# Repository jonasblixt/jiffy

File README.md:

# jiffy
IMX6UL Development board

This is a work in progress. The first version of the hardware works fine but some simplifications and polishing will be done for the R2 release.

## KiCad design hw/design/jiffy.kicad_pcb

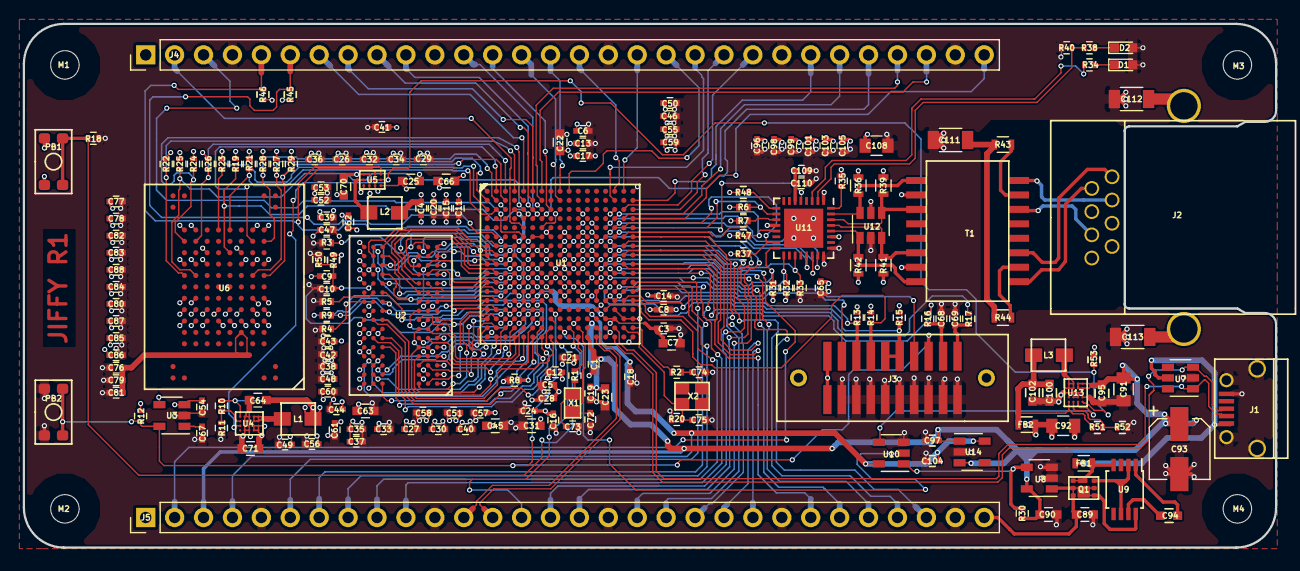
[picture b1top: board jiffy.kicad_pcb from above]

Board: 4 copper layers, 110.0 x 46.0 mm, 199 parts (0 on the bottom side), 190 nets.

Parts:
C1, C3, C4, C5, C6, C9, C10, C11, C12, C13, C14, C15, C16, C17, C18, C19, C20, C21, C24, C26, C27, C28, C29, C30, C32, C33, C34, C35, C36, C37, C38, C39, C40, C41, C42, C43, C44, C46, C47, C48, C49, C50, C51, C52, C53, C54, C55, C56, C57, C58, C59, C60, C61, C62, C65, C76, C77, C78, C79, C80, C81, C82, C83, C84, C85, C86, C87, C88, C96, C97, C98, C99, C101, C103, C104, C105, C109, C110: C0402_1u_10Vdc_X5R; C_0402
C7, C22, C23, C25, C31, C45: C0603_22u_10Vdc_X5R; C_0603
C8: C0402_10u_2.5Vdc_X5R; C_0402
C63, C64, C66, C71, C95, C100, C102: C0603_10u_10Vdc_X7R; C_0603
C67: C0402_100n_100Vdc_X5R; C_0402
C68, C69: C0402_10n_50Vdc_X7R; C_0402
C70: C0603_4u7_16Vdc_X7R; C_0603
C72, C73, C74, C75: C0402_15p_100Vdc_C0G; C_0402
C89, C90, C94: C0603_1u_25Vdc_X7R; C_0603
C91, C92: C0805_10u_25Vdc_X7R; C_0805
C93: PCAP_220u_11; CP_Elec_5x5.3
C108: C0805_20n_50Vdc_X7R; C_0805
C111, C112, C113: C1206_1n5_1000Vdc_X7R; C_1206
D1, D2: LED0402_SML-P11MTT86; LED_0603
FB1, FB2: BL0603_BLM18KG121TN1D; R_0603
J1: DX4R005JJ2R1800; USB_Micro-B
J2: RJE72-188-1401
J3: TFM-110-02-S-D-WT
J4, J5: Conn_01x30; Pin_Header_Straight_1x30_Pitch2.54mm
L1, L3: IHLP1212_470n_0; IHLP1212
L2: IHLP1212_1u_1; IHLP1212
M1, M2, M3, M4: MHNP_2.5mm; MH_2.5mm
PB1, PB2: KMR631NGULCLFS; kmr6
Q1: CSD17313Q2Q1; SON6_EP
R1, R2, R9, R16, R17: R0402_100R; R_0402
R3, R4, R10, R18, R19, R21, R22, R24, R25, R26, R27, R28, R29, R51, R53: R0402_46k40; R_0402
R5, R8: R0402_240R; R_0402
R6, R7, R12, R30, R33, R37, R40, R45, R46, R47, R48: R0402_10k; R_0402
R11: R0402_66k50; R_0402
R13, R14, R15: R0402_100k; R_0402
R20: R0402_2M20; R_0402
R23: R0402_22R; R_0402
R31, R32, R49, R50: R0402_1k50; R_0402
R34, R38: R0402_330R; R_0402
R35: R0402_12k10; R_0402
R36, R39, R41, R42: R0603_49R90; R_0603
R43, R44: R0603_75R; R_0603
R52: R0402_14k70; R_0402
T1: PT61018PEL; Ethernet_trafo_so16w
U1: MCIMX6G2AVM07; LFBGA289
U2: MT41K512M16HA-125; BGA-96_pitch0.8mm_dia0.4mm
U3: LP3470M5-3.08; SOT-23-5
U4, U13: FAN53541; WLCSP20
U5: FAN5355UC00; WLCSP12
U6: FEMC004GTTE7-T13-17; 100LBGA_DQ
U7, U12: USBLC6-4; SOT-23-6
U8: NCP360SNAET1G; SOT-23-5
U9: LM74610; TSSOP-8_3x3mm_Pitch0.65mm
U10: SN74AHC1G08; SOT-23-5
U11: LAN8710; QFN-32-1EP_5x5mm_Pitch0.5mm
U14: NCV551SN33T1G; SOT-23-5
X1: NX2012SA-32.768K-STD-MUB-1; NX2012
X2: NX2520SA-24.000000MHZ; NX2520

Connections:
/CPU/A0: U1.L5, U2.N3
/CPU/A1: U1.H2, U2.P7
/CPU/A2: U1.K1, U2.P3
/CPU/A3: U1.M2, U2.N2
/CPU/A4: U1.K4, U2.P8
/CPU/A5: U1.L1, U2.P2
/CPU/A6: U1.G2, U2.R8
/CPU/A7: U1.H4, U2.R2
/CPU/A8: U1.J4, U2.T8
/CPU/A9: U1.L2, U2.R3
/CPU/A10: U1.M4, U2.L7
/CPU/A11: U1.K3, U2.R7
/CPU/A12: U1.L4, U2.N7
/CPU/A13: U1.H3, U2.T3
/CPU/A14: U1.G1, U2.T7
/CPU/A15: U1.K5, U2.M7
/CPU/BM0: PB1.2, R18.1, U1.T10
/CPU/DQ0: U1.T4, U2.E3
/CPU/DQ1: U1.U6, U2.F7
/CPU/DQ2: U1.T6, U2.F2
/CPU/DQ3: U1.U7, U2.F8
/CPU/DQ4: U1.U8, U2.H7
/CPU/DQ5: U1.T8, U2.H8
/CPU/DQ6: U1.T5, U2.G2
/CPU/DQ7: U1.U4, U2.H3
/CPU/DQ8: U1.U2, U2.D7
/CPU/DQ9: U1.U3, U2.C3
/CPU/DQ10: U1.U5, U2.C8
/CPU/DQ11: U1.R4, U2.C2
/CPU/DQ12: U1.P5, U2.A7
/CPU/DQ13: U1.P3, U2.B8
/CPU/DQ14: U1.R2, U2.A2
/CPU/DQ15: U1.R1, U2.A3
/CPU/DRAM_CAS_B: U1.J2, U2.K3
/CPU/DRAM_CS0_B: U1.N2, U2.L2
/CPU/DRAM_DQM0: U1.T7, U2.E7
/CPU/DRAM_DQM1: U1.T3, U2.D3
/CPU/DRAM_ODT0: U1.N1, U2.K1
/CPU/DRAM_RAS_B: U1.M5, U2.J3
/CPU/DRAM_RESET: R3.1, U1.G4, U2.T2
/CPU/DRAM_SDBA0: U1.M1, U2.M2
/CPU/DRAM_SDBA1: U1.H1, U2.N8
/CPU/DRAM_SDBA2: U1.K2, U2.M3
/CPU/DRAM_SDCKE0: R4.1, U1.M3, U2.K9
/CPU/DRAM_SDCLK0_N: R9.1, U1.P2, U2.K7
/CPU/DRAM_SDCLK0_P: R9.2, U1.P1, U2.J7
/CPU/DRAM_SDQS0_N: U1.P7, U2.G3
/CPU/DRAM_SDQS0_P: U1.P6, U2.F3
/CPU/DRAM_SDQS1_N: U1.T2, U2.B7
/CPU/DRAM_SDQS1_P: U1.T1, U2.C7
/CPU/DRAM_SDWE_B: U1.J1, U2.L3
/CPU/DRAM_VREFDQ: C9.2, C10.1, R49.2, R50.1, U1.P4, U2.H1, U2.M8
/CPU/DRAM_ZQ0: R5.1, U2.L8
/CPU/DRAM_ZQPAD: R8.1, U1.N4
/CPU/DRX: R16.2, U1.J16
/CPU/DTX: R17.2, U1.J17
/CPU/ENET2_RX_DATA0: J4.21, U1.C17
/CPU/ENET2_RX_DATA1: J4.22, U1.C16
/CPU/ENET2_RX_EN: J4.24, U1.B17
/CPU/ENET2_RX_ER: J4.25, U1.D16
/CPU/ENET2_TX_CLK: J4.30, U1.D17
/CPU/ENET2_TX_DATA0: J4.16, U1.A15
/CPU/ENET2_TX_DATA1: J4.18, U1.A16
/CPU/ENET2_TX_EN: J4.20, U1.B15
/CPU/GPIO1_IO00: J5.2, U1.K13
/CPU/GPIO1_IO03: J5.6, U1.L17
/CPU/GPIO1_IO04: J5.7, U1.M16
/CPU/GPIO1_IO05: J5.8, U1.M17
/CPU/GPIO1_IO08: J5.9, U1.N17
/CPU/GPIO1_IO09: J5.10, U1.M15
/CPU/I2C1_SCL: J4.2, U1.E5
/CPU/I2C1_SDA: J4.3, U1.F5
/CPU/I2C2_SCL: J4.5, R46.2, U1.F3, U5.D3
/CPU/I2C2_SDA: J4.6, R45.2, U1.F2, U5.C3
/CPU/JTAG_TCK: J3.10, J3.12, R15.2, U1.M14
/CPU/JTAG_TDI: J3.6, R13.2, U1.N16
/CPU/JTAG_TDO: J3.14, U1.N15
/CPU/JTAG_TMS: J3.8, R14.2, U1.P14
/CPU/JTAG_TRST_N: J3.4, U1.N14
/CPU/LCD_DATA00: J4.14, U1.B9
/CPU/LCD_DATA01: J4.15, U1.A9
/CPU/LCD_DATA06: J4.19, U1.A10
/CPU/NAND_DATA00: J4.26, U1.D7
/CPU/NAND_DATA01: J4.27, U1.B7
/CPU/NAND_DATA02: J4.28, U1.A7
/CPU/NAND_DATA03: J4.12, U1.D6
/CPU/NAND_DATA04: J4.10, U1.C6
/CPU/NAND_DATA05: J4.9, U1.B6
/CPU/NAND_DATA06: J4.8, U1.A6
/CPU/NAND_DATA07: J4.7, U1.A5
/CPU/NAND_WE_B: J4.13, U1.C8
/CPU/NVCC_PLL: C8.1, U1.P13
/CPU/P3V3_PG: R53.2, U4.A2, U5.B2, U5.C2, U5.D2, U13.A1
/CPU/POWER_REQ: U1.T9, U10.2
/CPU/RST_N: J3.16, PB2.2, R12.2, U1.P8, U3.5
/CPU/UART1_CTS_B: J5.28, U1.K15
/CPU/UART1_RTS_B: J5.27, U1.J14
/CPU/UART1_RX_DATA: J5.26, U1.K16
/CPU/UART1_TX_DATA: J5.25, U1.K14
/CPU/UART3_CTS_B: J5.15, U1.H15
/CPU/UART3_RTS_B: J5.16, U1.G14
/CPU/UART3_RX_DATA: J5.22, U1.H16
/CPU/UART3_TX_DATA: J5.24, U1.H17
/CPU/UART4_RX_DATA: J5.20, U1.G16
/CPU/UART4_TX_DATA: J5.21, U1.G17
/CPU/UART5_RX_DATA: J5.18, U1.G13
/CPU/UART5_TX_DATA: J5.19, U1.F17
/CPU/USB_OTG2_D_N: J5.13, U1.T13
/CPU/USB_OTG2_D_P: J5.12, U1.U13
/CPU/VDD_ARM_CAP: C6.1, C13.1, C17.1, C22.1, U1.G9, U1.G10, U1.G11, U1.H11
/CPU/VDD_HIGH_CAP: C3.1, C7.1, U1.N6, U1.R14, U1.R15
/CPU/VDD_SNVS_CAP: C14.1, U1.N12
/CPU/VDD_SOC_CAP: C5.1, C12.1, C16.1, C21.1, C24.1, C28.1, C31.1, U1.G8, U1.H8, U1.J8, U1.J11, U1.K8, U1.K11, U1.L8, U1.L9, U1.L10, U1.L11
/CPU/VDD_USB_CAP: C19.1, C23.1, U1.R12
/CPU/WUP_N: J5.14, U1.R8
/CPU/eMMC_CLK: R23.2, U1.C1
/CPU/eMMC_CLK_2: R23.1, U6.P6
/CPU/eMMC_CMD: R21.2, U1.C2, U6.P5
/CPU/eMMC_D0: R29.2, U1.B3, U6.K2
/CPU/eMMC_D1: R28.2, U1.B2, U6.N2
/CPU/eMMC_D2: R27.2, U1.B1, U6.K3
/CPU/eMMC_D3: U1.A2, U6.N3
/CPU/eMMC_D4: R26.2, U1.A3, U6.N8
/CPU/eMMC_D5: R25.2, U1.C5, U6.K8
/CPU/eMMC_D6: R24.2, U1.B5, U6.N9
/CPU/eMMC_D7: R22.2, U1.A4, U6.K9
/CPU/eMMC_RST_N: R19.2, U1.D5, U6.M5
/CPU/eMMC_VDDIM: C76.1, C79.1, C81.1, U6.E4
/CR: C109.1, C110.1, U11.6
/ENET_CLK: U1.F14, U11.5
/ENET_CRS_DV: R37.2, U1.E16, U11.15
/ENET_MDC: R32.1, U1.L16, U11.17
/ENET_MDIO: R31.1, U1.K17, U11.16
/ENET_RST_N: R33.1, U1.J15, U11.19
/ENET_RXD0: R7.2, U1.F16, U11.11
/ENET_RXD1: R6.2, U1.E17, U11.10
/ENET_RXER: R47.2, U1.D15, U11.13
/ENET_TXD0: U1.E15, U11.22
/ENET_TXD1: U1.E14, U11.23
/ENET_TXEN: U1.F15, U11.21
/P3V3_EN: U10.4, U13.A2
/USB_D_N: J1.2, U1.T15, U7.1
/USB_D_P: J1.3, U1.U15, U7.3
/USB_VBUS: FB1.1, J1.1, U7.5
/USB_VBUS_2: C89.1, J5.30, Q1.1, Q1.2, Q1.5, Q1.6, Q1.7, U8.1, U9.8
GND: C1.2, C3.2, C4.2, C5.2, C6.2, C7.2, C8.2, C10.2, C11.2, C12.2, C13.2, C14.2, C15.2, C16.2, C17.2, C18.2, C19.2, C20.2, C21.2, C22.2, C23.2, C24.2, C25.2, C26.2, C27.2, C28.2, C29.2, C30.2, C31.2, C32.2, C33.2, C34.2, C35.2, C36.2, C37.2, C38.2, C39.2, C40.2, C41.2, C42.2, C43.2, C44.2, C45.2, C46.2, C47.2, C48.2, C49.2, C50.2, C51.2, C52.2, C53.2, C54.2, C55.2, C56.2, C57.2, C58.2, C59.2, C60.2, C61.2, C62.2, C63.2, C64.2, C65.2, C66.2, C67.2, C68.2, C69.2, C70.2, C71.2, C72.2, C73.2, C74.2, C75.2, C76.2, C77.2, C78.2, C79.2, C80.2, C81.2, C82.2, C83.2, C84.2, C85.2, C86.2, C87.2, C88.2, C89.2, C90.2, C91.2, C92.2, C93.2, C95.2, C96.2, C97.2, C98.2, C99.2, C100.2, C101.2, C102.2, C103.2, C104.2, C105.2, C108.2, C109.2, C110.2, C111.2, C112.2, C113.2, D1.2, D2.2, J1.5, J1.6, J3.3, J3.5, J3.7, J3.9, J3.11, J3.13, J3.15, J3.17, J3.19, J4.4, J4.11, J4.17, J4.23, J4.29, J5.5, J5.11, J5.17, J5.23, J5.29, PB2.1, R3.2, R4.2, R5.2, R8.2, R11.2, R18.2, R20.2, R33.2, R35.2, R40.2, R50.2, R52.2, U1.A1, U1.A17, U1.C3, U1.C7, U1.C11, U1.C15, U1.E8, U1.E11, U1.F6, U1.F7, U1.F8, U1.F9, U1.F10, U1.F11, U1.F12, U1.G3, U1.G5, U1.G7, U1.G12, U1.G15, U1.H7, U1.H12, U1.J5, U1.J7, U1.J12, U1.K7, U1.K12, U1.L3, U1.L7, U1.L12, U1.M7, U1.M8, U1.M9, U1.M10, U1.M11, U1.M12, U1.N3, U1.N5, U1.N7, U1.P15, U1.R3, U1.R5, U1.R7, U1.R11, U1.R16, U1.R17, U1.T14, U1.U1, U1.U14, U1.U17, U2.A9, U2.B1, U2.B3, U2.B9, U2.D1, U2.D8, U2.E1, U2.E2, U2.E8, U2.F9, U2.G1, U2.G8, U2.G9, U2.J2, U2.J8, U2.M1, U2.M9, U2.P1, U2.P9, U2.T1, U2.T9, U3.2, U4.B1, U4.B2, U4.B3, U4.B4, U4.C1, U4.C2, U4.C3, U4.C4, U5.A1, U5.B1, U5.C1, U6.G2, U6.G3, U6.G4, U6.G5, U6.G6, U6.G7, U6.G8, U6.G9, U6.H2, U6.H9, U6.L3, U6.L8, U6.M4, U6.M7, U6.P2, U6.P9, U7.2, U8.2, U8.3, U10.3, U11.24, U11.25, U11.33, U12.2, U13.B1, U13.B2, U13.B3, U13.B4, U13.C1, U13.C2, U13.C3, U13.C4, U14.2
unnamed: C67.1, U3.1
unnamed: C68.1, J3.18, R16.1
unnamed: C69.1, J3.20, R17.1
unnamed: C72.1, U1.T11, X1.1
unnamed: C73.1, R1.2, X1.3
unnamed: C74.1, R2.2, X2.1
unnamed: C75.1, R20.1, U1.T16, X2.3
unnamed: C94.1, U9.7
unnamed: C94.2, U9.1
unnamed: C100.1, C102.1, FB2.1, L3.1, R51.1, U13.A4
unnamed: C111.1, R43.1, R44.1
unnamed: C112.1, J2.9
unnamed: C113.1, J2.10
unnamed: D1.1, R34.2
unnamed: D2.1, R38.2
unnamed: FB1.2, Q1.4, Q1.8, U9.4
unnamed: J2.1, T1.11
unnamed: J2.2, T1.9
unnamed: J2.3, T1.16
unnamed: J2.6, T1.14
unnamed: L1.2, U4.D3, U4.D4, U4.E3, U4.E4
unnamed: L2.2, U5.A2
unnamed: L3.2, U13.D3, U13.D4, U13.E3, U13.E4
unnamed: Q1.3, U9.2, U9.6
unnamed: R1.1, U1.U11
unnamed: R2.1, U1.T17
unnamed: R10.2, R11.1, U4.A3
unnamed: R30.2, U8.4, U10.1
unnamed: R34.1, U11.3
unnamed: R35.1, U11.32
unnamed: R36.2, T1.1, U11.31, U12.6
unnamed: R38.1, R40.1, U11.2
unnamed: R39.2, T1.3, U11.30, U12.4
unnamed: R41.2, T1.6, U11.29, U12.3
unnamed: R42.2, T1.8, U11.28, U12.1
unnamed: R43.2, T1.15
unnamed: R44.2, T1.10
unnamed: R48.2, U11.9
unnamed: R51.2, R52.1, U13.A3
P1V4: C4.1, C11.1, C15.1, C20.1, C25.1, C66.1, L2.1, U1.H9, U1.H10, U1.J9, U1.J10, U1.K9, U1.K10, U5.D1
P1V35: C9.1, C27.1, C30.1, C33.1, C35.1, C37.1, C38.1, C39.1, C40.1, C42.1, C43.1, C44.1, C45.1, C47.1, C48.1, C49.1, C51.1, C52.1, C53.1, C56.1, C57.1, C58.1, C60.1, C61.1, C62.1, C63.1, C64.1, L1.1, R10.1, R49.1, U1.G6, U1.H6, U1.J6, U1.K6, U1.L6, U1.M6, U2.A1, U2.A8, U2.B2, U2.C1, U2.C9, U2.D2, U2.D9, U2.E9, U2.F1, U2.G7, U2.H2, U2.H9, U2.K2, U2.K8, U2.N1, U2.N9, U2.R1, U2.R9, U4.A4
P3V3: C26.1, C29.1, C32.1, C34.1, C36.1, C41.1, C46.1, C50.1, C54.1, C55.1, C59.1, C65.1, C70.1, C71.1, C77.1, C78.1, C80.1, C82.1, C83.1, C84.1, C85.1, C86.1, C87.1, C88.1, C92.1, C96.1, C98.1, C99.1, C101.1, C103.1, C105.1, C108.1, FB2.2, J3.1, J3.2, J4.1, J5.1, PB1.1, R6.1, R7.1, R12.1, R13.1, R14.1, R15.1, R19.1, R21.1, R22.1, R24.1, R25.1, R26.1, R27.1, R28.1, R29.1, R31.2, R32.2, R36.1, R37.1, R39.1, R41.1, R42.1, R45.1, R46.1, R47.1, R48.1, R53.1, T1.2, T1.7, U1.C4, U1.E7, U1.E13, U1.F4, U1.F13, U1.H13, U1.J13, U1.L13, U1.M13, U1.N13, U3.3, U3.4, U4.D1, U4.D2, U4.E1, U4.E2, U5.A3, U5.B3, U6.F2, U6.F3, U6.F4, U6.F5, U6.F6, U6.F7, U6.F8, U6.F9, U6.H3, U6.H8, U6.L2, U6.L4, U6.L7, U6.L9, U6.P3, U6.P8, U11.1, U11.12, U11.27, U12.5
P3V3_PERM: C18.1, C104.1, J5.4, U1.P12, U10.5, U14.5
P5V0: C1.1, C90.1, C91.1, C93.1, C95.1, C97.1, J5.3, R30.1, U1.T12, U1.U12, U8.5, U13.D1, U13.D2, U13.E1, U13.E2, U14.1, U14.3

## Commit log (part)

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2018-02-04 Removed ds_store-files
2018-02-17 R1 Release
2019-04-07 cleanup
2019-04-07 Added license file
2019-04-07 Add gitattributes
